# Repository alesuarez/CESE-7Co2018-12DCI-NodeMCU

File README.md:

CESE-7Co2018-12DCI
===================

Replica nodeMCU
---------------

- https://github.com/nodemcu/nodemcu-devkit-v1.0

## Designator & Parameter

|Designator|Parameter|
|-|-|
|C1,C4,C6 |100nF (104) ±10% 16V|
|C2 |100uF(107) ±10% 6.3V Case B 3528|
|C3,C5,C8 |10uF(106) ±20% 10V |
|C7|10uF(106) ±10% 25V|
|D1|SOD-123 40V,1A,VF=0.45V@1A|
|LED1|1.6x0.8x0.6 Iv= 35~65mcd @IF=5mA ESD:1000V |
|R1,R2,R3,R4,R5,R7,R8|12KΩ (1202) ±1% 0.0625W [50V TYP] [100V MAX] T.C.R ±100|
|R6,R9,R11,R12|470Ω (4700) ±1% 0.0625W [50V TYP] [100V MAX] T.C.R ±100|
|R10(Do not install)|0Ω (0R00) ±1% 0.0625W [50V TYP] [100V MAX] T.C.R ±100|
|R13|220kΩ (2203) ±1% 0.0625W [50V TYP] [100V MAX] T.C.R ±100|
|R14|100kΩ (1003) ±1% 0.0625W [50V TYP] [100V MAX] T.C.R ±100|

Diseño de circuitos integrados
------------------------------

### AUTOR ###

- Suarez, Sebastian Alejandro

### REVISOR ###

- Ferreyra, Hernan

DISEÑO
------

Ver carperta OUT

Planilla de revision
--------------------

https://docs.google.com/spreadsheets/d/1GdUnNvNa7OGYix6WSLJ_TsLkDbuR13YAUQkwYhvH5Zk/edit?usp=sharing

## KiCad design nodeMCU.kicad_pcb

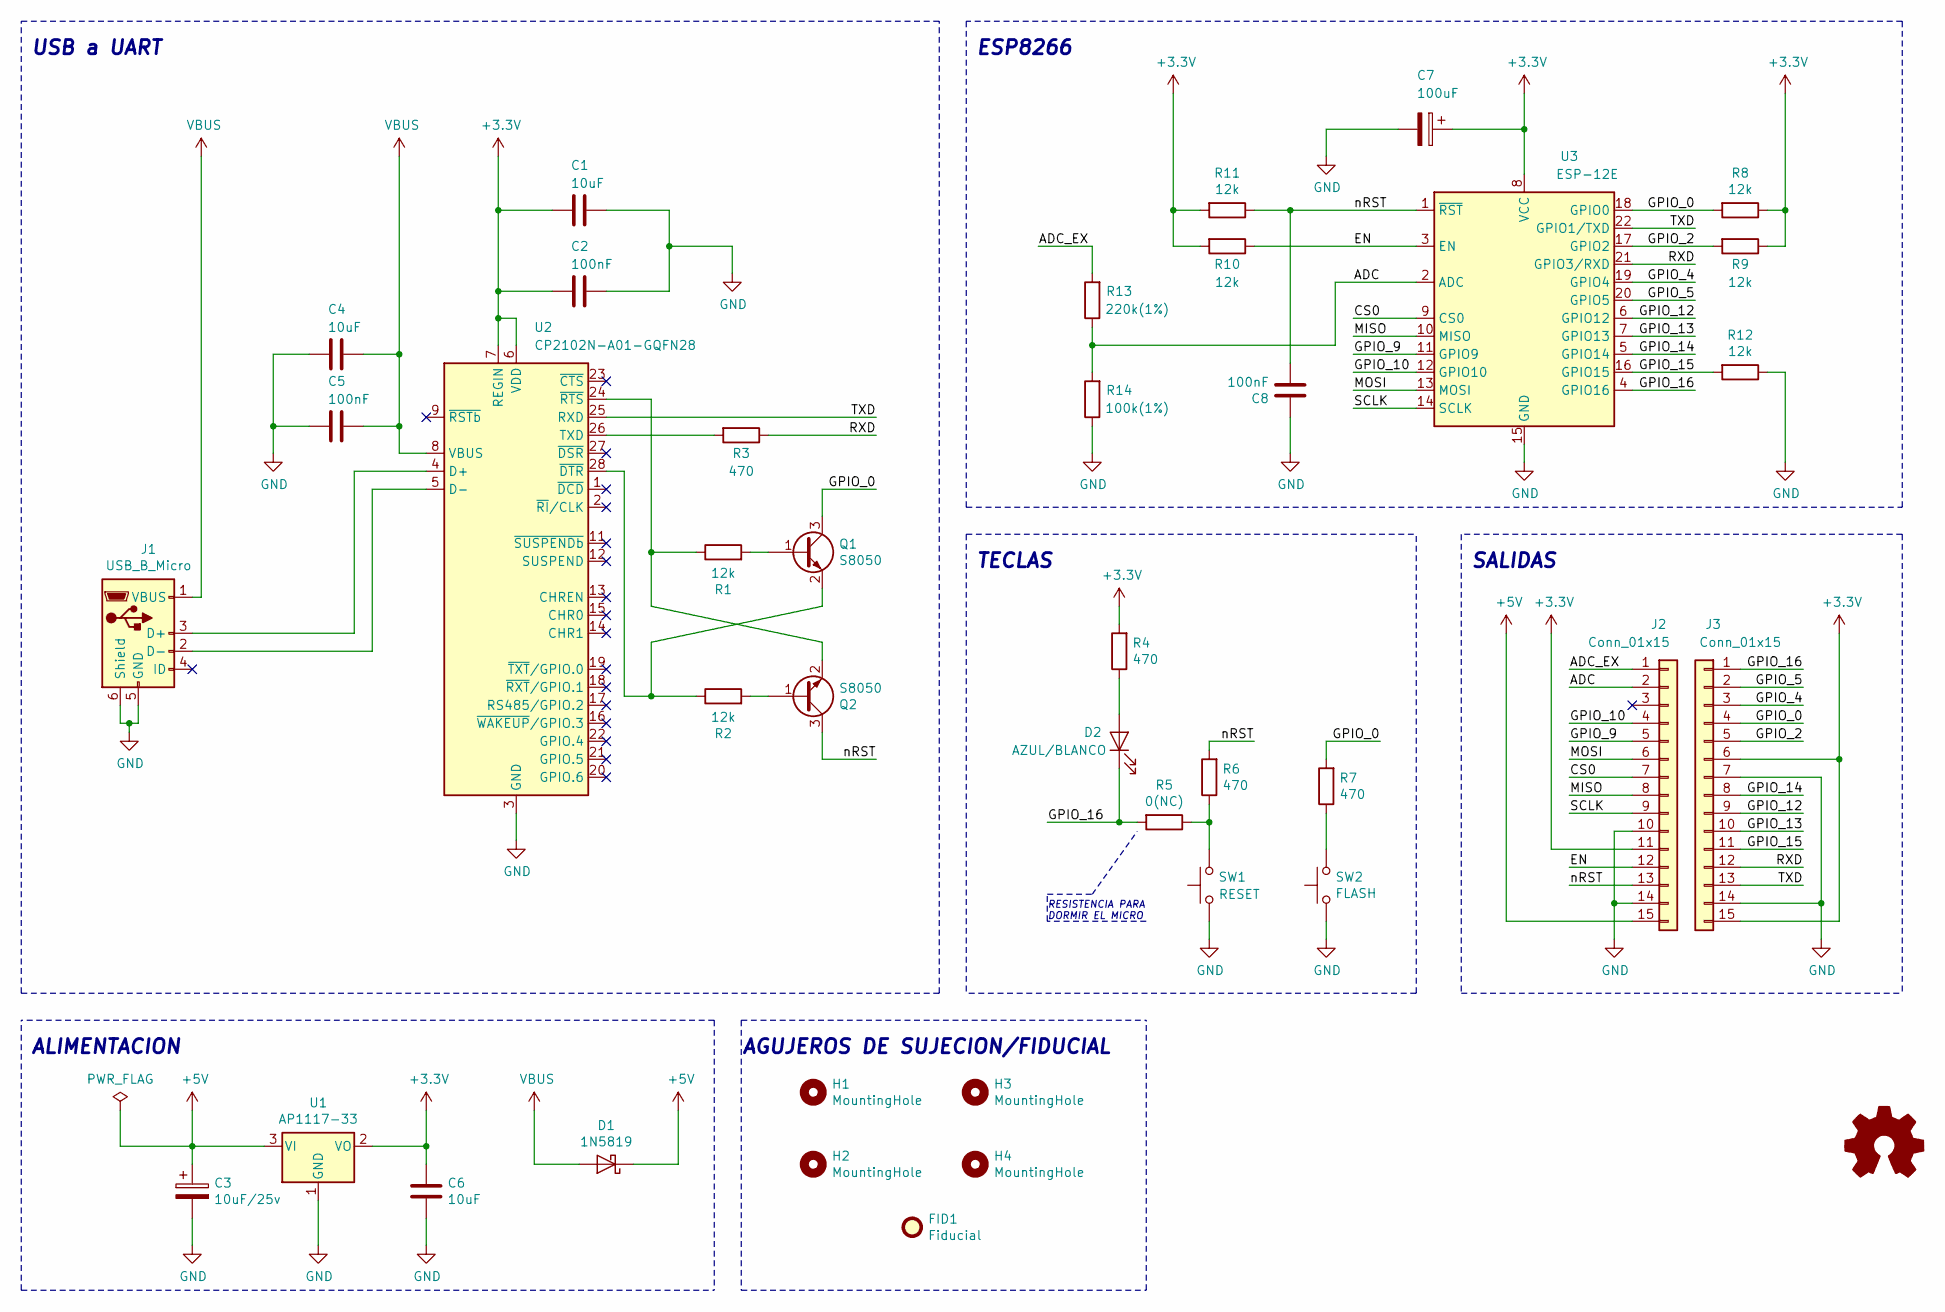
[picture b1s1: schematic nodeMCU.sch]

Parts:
C1, C4, C6: 10uF; C_0402_1005Metric
C2, C5, C8: 100nF; C_0402_1005Metric
C3: 10uF/25v; C_0805_2012Metric
C7: 100uF; CP_EIA-3528-21_Kemet-B
D1: 1N5819; D_SOD-323_HandSoldering
D2: AZUL/BLANCO; LED_0603_1608Metric
FID1: Fiducial; Fiducial_1mm_Mask2mm
H1, H2, H3, H4: MountingHole; MountingHole_2.2mm_M2
J1: USB_B_Micro; USB_Micro-B_Molex-105017-0001
J2, J3: Conn_01x15; PinHeader_1x15_P2.54mm_Vertical
Q1, Q2: S8050; SOT-23
R1, R2, R8, R9, R10, R11, R12: 12k; R_0402_1005Metric
R3, R4, R6, R7: 470; R_0402_1005Metric
R5: 0(NC); R_0402_1005Metric
R13: 220k(1%); R_0402_1005Metric
R14: 100k(1%); R_0402_1005Metric
SW1: RESET; SW_Push_SPST_NO_Alps_SKRK
SW2: FLASH; SW_Push_SPST_NO_Alps_SKRK
U1: AP1117-33; SOT-223-3_TabPin2
U2: CP2102N-A01-GQFN28; QFN-28-1EP_5x5mm_P0.5mm_EP3.35x3.35mm
U3: ESP-12E

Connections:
+3V3: C1.2, C2.2, C6.1, C7.1, J2.11, J3.6, J3.15, R4.2, R8.1, R9.1, R10.2, R11.2, U1.2 (VO), U2.6 (VDD), U2.7 (REGIN), U3.8 (VCC)
+5V: C3.1, D1.1 (K), J2.15, U1.3 (VI)
/ADC: J2.2, R13.1, R14.2, U3.2 (ADC)
/ADC_EX: J2.1, R13.2
/CS0: J2.7, U3.9 (CS0)
/EN: J2.12, R10.1, U3.3 (EN)
/GPIO_0: J3.4, Q1.3 (C), R7.2, R8.2, U3.18 (GPIO0)
/GPIO_2: J3.5, R9.2, U3.17 (GPIO2)
/GPIO_4: J3.3, U3.19 (GPIO4)
/GPIO_5: J3.2, U3.20 (GPIO5)
/GPIO_9: J2.5, U3.11 (GPIO9)
/GPIO_10: J2.4, U3.12 (GPIO10)
/GPIO_12: J3.9, U3.6 (GPIO12)
/GPIO_13: J3.10, U3.7 (GPIO13)
/GPIO_14: J3.8, U3.5 (GPIO14)
/GPIO_15: J3.11, R12.2, U3.16 (GPIO15)
/GPIO_16: D2.1 (K), J3.1, R5.2, U3.4 (GPIO16)
/MISO: J2.8, U3.10 (MISO)
/MOSI: J2.6, U3.13 (MOSI)
/RXD: J3.12, R3.1, U3.21 (GPIO3/RXD)
/SCLK: J2.9, U3.14 (SCLK)
/TXD: J3.13, U2.25 (RXD), U3.22 (GPIO1/TXD)
/nDTR_CP: Q1.2 (E), R2.1, U2.28 (~DTR)
/nRST: C8.2, J2.13, Q2.3 (C), R6.2, R11.1, U3.1 (~RST)
/nRTS_CP: Q2.2 (E), R1.1, U2.24 (~RTS)
GND: C1.1, C2.1, C3.2, C4.2, C5.2, C6.2, C7.2, C8.1, J1.5 (GND), J1.6 (Shield), J2.10, J2.14, J3.7, J3.14, R12.1, R14.1, SW1.1, SW2.1, U1.1 (GND), U2.3 (GND), U2.29 (GND), U3.15 (GND)
unnamed: D2.2 (A), R4.1
unnamed: J1.2 (D-), U2.5 (D-)
unnamed: J1.3 (D+), U2.4 (D+)
unnamed: Q1.1 (B), R1.2
unnamed: Q2.1 (B), R2.2
unnamed: R3.2, U2.26 (TXD)
unnamed: R5.1, R6.1, SW1.2
unnamed: R7.1, SW2.2
VBUS: C4.1, C5.1, D1.2 (A), J1.1 (VBUS), U2.8 (VBUS)

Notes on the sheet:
USB a UART
ESP8266
AGUJEROS DE SUJECION/FIDUCIAL
SALIDAS
TECLAS
RESISTENCIA PARA DORMIR EL MICRO
ALIMENTACION

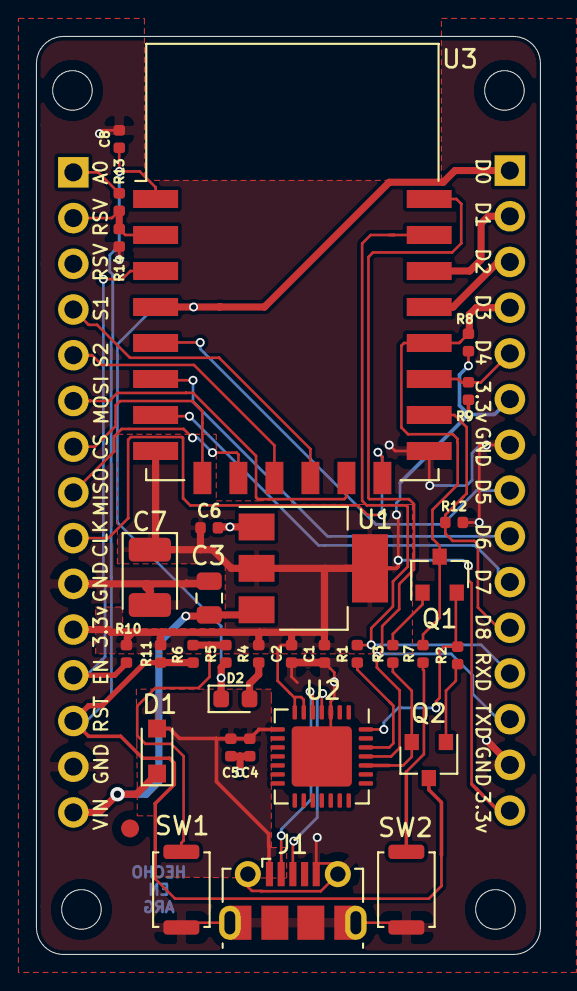
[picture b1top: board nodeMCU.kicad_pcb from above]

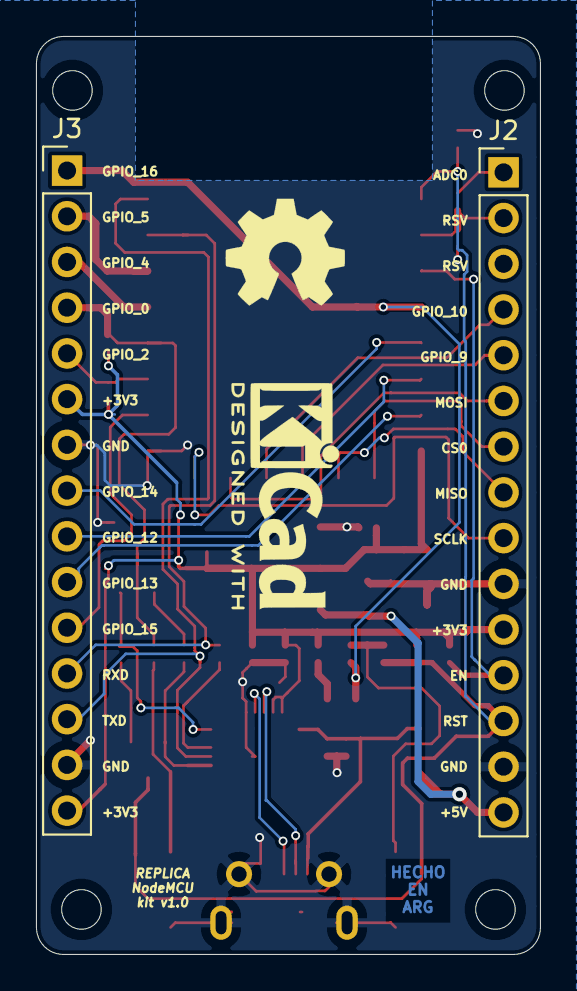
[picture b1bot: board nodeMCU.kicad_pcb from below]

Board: 2 copper layers, 28.0 x 51.0 mm, 39 parts (2 on the bottom side), 35 nets.

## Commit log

2019-06-08 Esquematico sin etiquetas - Una sola hoja
2019-06-12 Primera version de esquematico terminada
2019-06-16 Terminada la revision 1.1 + rule check
2019-06-20 Agrego valores a los componentes
2019-06-20 Agrego footprints
2019-06-20 Ubicacion componentes en la placa + corte curvo del PCB
2019-06-20 Agrego agujeros de sujecion esquematico + pcb
2019-06-20 Arreglo bordes de corte redondeados + ubico agujeros de sujecion
2019-06-20 Corrijo footprint de diodo D1
2019-06-21 Comienzo el ruteo
2019-06-22 Cambios propuesto por el docente en el esquematico
2019-06-22 Agrego mas cambios propuestos por el docente en el esquematico
2019-06-22 Borro ruteo
2019-06-22 Termino el ruteo
2019-06-23 Agregp logos
2019-06-23 Agrego bvistas 3ds
2019-06-23 PCB Terminado
2019-06-26 Agrego fiducial
2019-06-26 Agrego vistas 3d
2019-06-26 Agrego numero de partes
2019-06-26 Agrego numeros de parte y numero de digikey
2019-06-26 Terminado el PCB
2019-06-29 Agrego comentarios del Docente
2019-07-01 Correcciones propuestas II
2019-07-01 Correcciones finales segun el docente
2019-07-01 Agrego pdf
2019-07-01 Terminada version 1.3v
2019-08-18 Actualizo vistas
